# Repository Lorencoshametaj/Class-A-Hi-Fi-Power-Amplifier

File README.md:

# Class-A-Hi-Fi-Power-Amplifier
10 W Class A Hi-Fi Power Amplifier...

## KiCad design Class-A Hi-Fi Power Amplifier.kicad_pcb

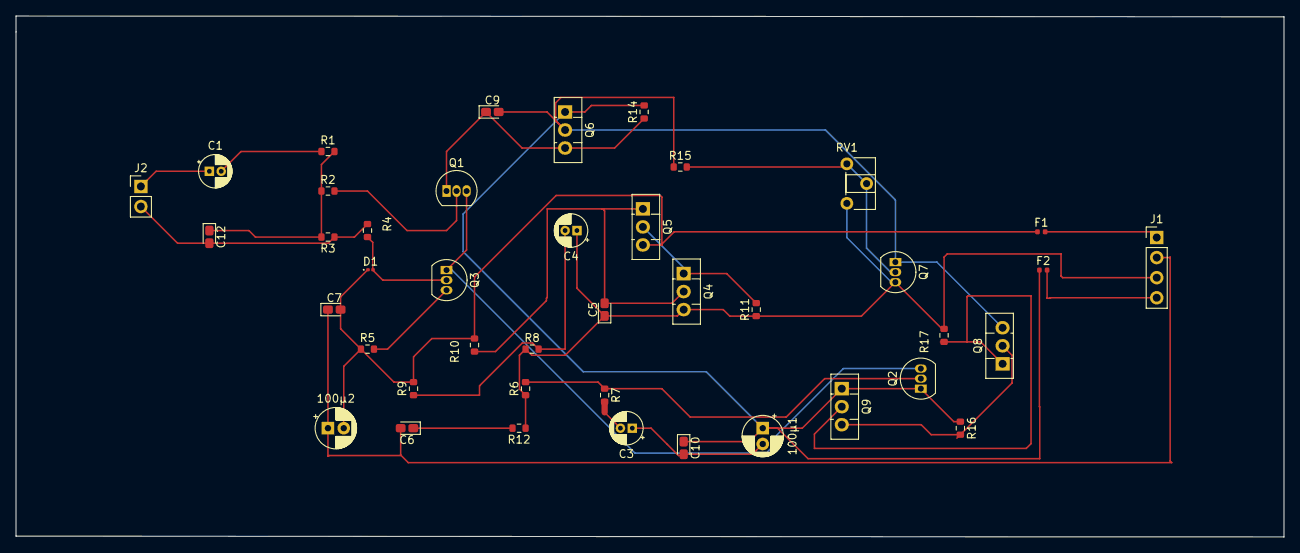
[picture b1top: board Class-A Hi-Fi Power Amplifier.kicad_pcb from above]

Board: 2 copper layers, 160.4 x 65.9 mm, 42 parts (0 on the bottom side), 26 nets.

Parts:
100µ1, 100µ2: C_Polarized; CP_Radial_D5.0mm_P2.00mm
C1: 4.7µ; CP_Radial_D4.0mm_P1.50mm
C3, C4: 100µ; CP_Radial_D4.0mm_P1.50mm
C5, C9, C12: 100p; CP_EIA-1608-10_AVX-L_Pad1.25x1.05mm_HandSolder
C6, C7, C10: 100n; CP_EIA-1608-10_AVX-L_Pad1.25x1.05mm_HandSolder
D1: LED; D_0201_0603Metric
F1, F2: 3A; Fuse_0402_1005Metric
J1: PinHeader_1x04_P2.54mm_Vertical
J2: PinHeader_1x02_P2.54mm_Vertical
Q1, Q2, Q3, Q7: BC546; TO-92_Inline
Q4, Q6: BD140; TO-126-3_Vertical
Q5: MJL4281; TO-126-3_Vertical
Q8: BD139; TO-126-3_Vertical
Q9: MJL4302; TO-126-3_Vertical
R1, R2, R7, R15: 1k; R_0603_1608Metric
R3, R4, R6: 22k; R_0603_1608Metric
R5, R14: 560; R_0603_1608Metric
R8, R9: 3k3; R_0603_1608Metric
R10, R16: 220; R_0603_1608Metric
R11, R17: 0R33; R_0603_1608Metric
R12: 10; R_0603_1608Metric
RV1: 2k; Potentiometer_ACP_CA6-H2,5_Horizontal

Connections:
Earth: 100µ1.2, C3.1, C10.2
unnamed: C1.2, R1.1
unnamed: C3.2, R7.2
unnamed: C4.2, R8.2, R9.1
unnamed: C6.1, R12.2
unnamed: C12.1, R1.2, R2.1, R3.2
unnamed: D1.2 (A), Q3.2 (B), R4.2
unnamed: 100µ2.2, C7.2, D1.1 (K), F1.1, Q5.3 (E), R5.1, R9.2, R10.2
unnamed: F1.2, J1.1
unnamed: 100µ2.1, C6.2, C7.1, J1.2
unnamed: C4.1, C5.1, J1.3, Q4.3 (B), Q7.3 (E), R6.1, R8.1, R11.1, R12.1, R17.2, RV1.3
unnamed: F2.2, J1.4
unnamed: C1.1, J2.1
unnamed: C12.2, J2.2, R3.1, R4.1
unnamed: Q1.2 (B), R2.2
unnamed: C9.1, Q1.1 (C), Q6.3 (B), R14.1
unnamed: Q1.3 (E), Q2.3 (E), Q3.1 (C)
unnamed: Q2.2 (B), R6.2, R7.1
unnamed: 100µ1.1, C10.1, F2.1, Q2.1 (C), Q6.1 (E), Q9.1 (E), R14.2, R16.1
unnamed: Q3.3 (E), R5.2
unnamed: C5.2, Q4.2 (C), Q5.1 (B), R10.1
unnamed: Q4.1 (E), Q5.2 (C), R11.2
unnamed: C9.2, Q6.2 (C), Q7.1 (C), Q8.3 (B), R15.1
unnamed: Q7.2 (B), R15.2, RV1.1, RV1.2
unnamed: Q8.2 (C), Q9.3 (B), R16.2
unnamed: Q8.1 (E), Q9.2 (C), R17.1

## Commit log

2024-09-26 First Release
